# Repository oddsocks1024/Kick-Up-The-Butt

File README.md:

# Kick-Up-The-Butt - C64 / VIC20 Reset Cartridge

## Description
A C64 / VIC20 reset cartridge with pass-through and a 3D printable case. Kick-Up-The-Butt! plugs into the user port and provides a simple reset button

## Bill of Materials

| Qty | Component                                                         |
|:---:|-------------------------------------------------------------------|
| 1   | 6x6mm Tactile Button - ideally tall (or use optional reset pin)   |
| 1   | 805-24P Connector - 24pin for C64 / VIC20 User Port               |

* Ideally a tall tactile button should be used, but if you only have short ones you can 3D print the STL reset pin and use that to extend it.
* When attaching the 805-24P connector, gently bend the pins with pliers so they touch the pads on both sides. Make sure the PCB is straight before soldering.

## 3D Printable Case
A 3D printable case has been specifcally designed for this PCB and the STLs are included in the repo.

* Insert the PCB into the bottom case part, aligning the holes in the PCB with screw posts.
* Align the top part of the case with the bottom. (If using a reset pin, insert it before aligning).
* Screw together using 2 x 3.5mm self-tapping screws. Maximum length about 15mm.

---

## Support Me
Everything is freely available so you can make your own PCB and case, however if you would like to support me, please see the following links. 

* [My Projects](https://projects.amiga-hardware.com) - Donate on this page
* [Order the Kick-Up-The-Butt PCB](https://www.pcbway.com/project/shareproject/Kick_Up_The_Butt_User_Port_Reset_Cart_for_C64_VIC_20_fc886e20.html)
* [Order the Kick-Up-The-Butt Case](https://www.pcbway.com/project/shareproject/Kick_Up_The_Butt_User_Port_Reset_Cart_for_C64_VIC_20_Case_bae8bbd3.html)

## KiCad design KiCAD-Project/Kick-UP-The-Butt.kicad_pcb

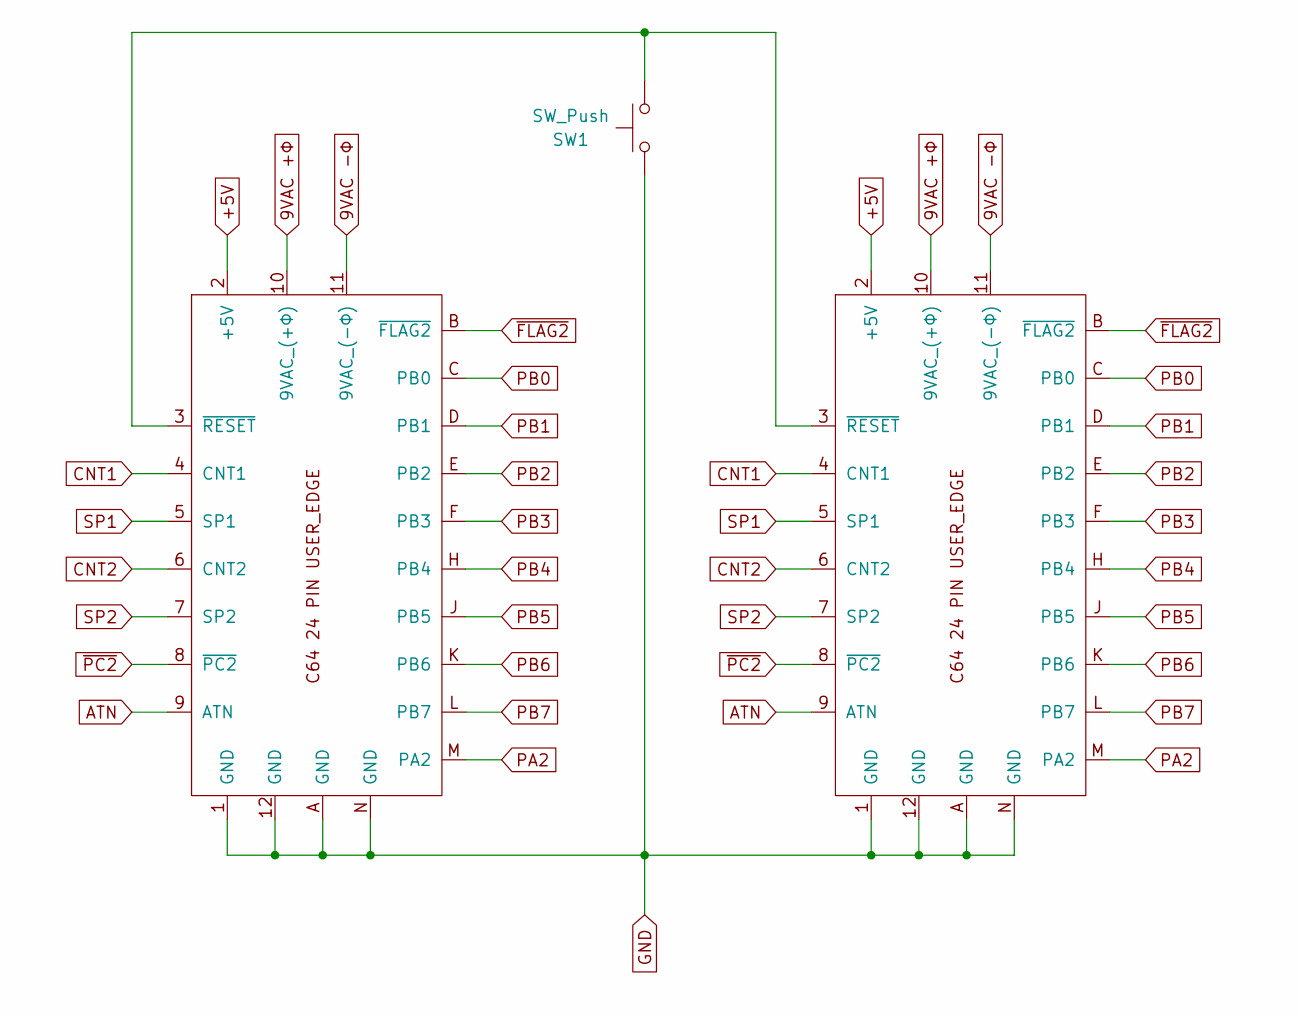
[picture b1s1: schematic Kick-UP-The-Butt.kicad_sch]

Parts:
CN1: C64 User Port Connector; C64 User Edge
CN2: C64 User Port Connector; C64 User Pads
SW1: SW_Push; SW_PUSH_6mm

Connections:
9VAC +Φ: CN1.10 (9VAC_(+Φ)), CN2.10 (9VAC_(+Φ))
9VAC -Φ: CN1.11 (9VAC_(-Φ)), CN2.11 (9VAC_(-Φ))
+5V: CN1.2 (+5V), CN2.2 (+5V)
ATN: CN1.9 (ATN), CN2.9 (ATN)
CNT1: CN1.4 (CNT1), CN2.4 (CNT1)
CNT2: CN1.6 (CNT2), CN2.6 (CNT2)
GND: CN1.1 (GND), CN1.12 (GND), CN1.A (GND), CN1.N (GND), CN2.1 (GND), CN2.12 (GND), CN2.A (GND), CN2.N (GND), SW1.1
unnamed: CN1.3 (~RESET), CN2.3 (~RESET), SW1.2
PA2: CN1.M (PA2), CN2.M (PA2)
PB0: CN1.C (PB0), CN2.C (PB0)
PB1: CN1.D (PB1), CN2.D (PB1)
PB2: CN1.E (PB2), CN2.E (PB2)
PB3: CN1.F (PB3), CN2.F (PB3)
PB4: CN1.H (PB4), CN2.H (PB4)
PB5: CN1.J (PB5), CN2.J (PB5)
PB6: CN1.K (PB6), CN2.K (PB6)
PB7: CN1.L (PB7), CN2.L (PB7)
SP1: CN1.5 (SP1), CN2.5 (SP1)
SP2: CN1.7 (SP2), CN2.7 (SP2)
~FLAG2: CN1.B (~FLAG2), CN2.B (~FLAG2)
~PC2: CN1.8 (~PC2), CN2.8 (~PC2)

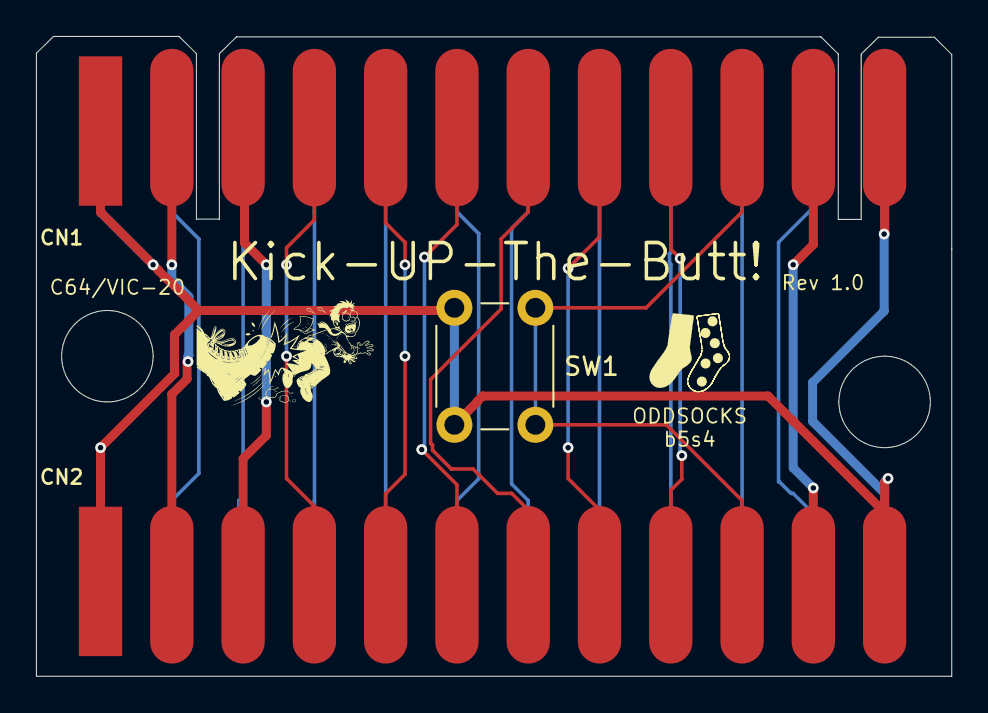
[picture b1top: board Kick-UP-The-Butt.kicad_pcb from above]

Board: 2 copper layers, 50.8 x 35.5 mm, 3 parts (0 on the bottom side), 21 nets.

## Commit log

2026-03-08 Added PCB URL
